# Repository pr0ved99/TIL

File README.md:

# TIL · 이영현의 기술 학습 기록

SSAFY 임베디드 로봇 트랙에서 시작한 학습 기록입니다. 데이터시트에서 읽은 동작을 보드에서 확인하고, 실험을 다시 해 볼 수 있도록 코드와 관측 결과를 함께 남깁니다.

## 대표 프로젝트 · Tracked Mobile Robot

브라우저의 무선 주행 명령이 STM32를 거쳐 좌우 궤도를 움직이는 로봇입니다. 프로젝트 README에서 실제 차체의 움직임, 펌웨어의 정지 판단, Gazebo 속 자율주행을 각각 확인할 수 있습니다. **[프로젝트 열기](https://github.com/pr0ved99/TIL/tree/agent/dual-encoder-bringup/Projects/Tracked_Mobile_Robot#readme)**

| 궁금한 점 | 바로 보기 |
| --- | --- |
| 실제 로봇은 어떻게 움직이나요? | [카펫 주행·비상정지·복구 MP4 (2분 29초)](https://raw.githubusercontent.com/pr0ved99/TIL/refs/heads/agent/dual-encoder-bringup/Projects/Tracked_Mobile_Robot/assets/videos/wifi_mvp/2026-10-24/final/TMR_MVP_Final_2026-10-24.mp4) |
| 정지 명령을 받으면 출력이 언제 꺼지나요? | [STM32 두 PWM의 차단 파형과 측정 기준](https://github.com/pr0ved99/TIL/blob/agent/dual-encoder-bringup/Projects/Tracked_Mobile_Robot/docs/verification/10_STM32_Active_DISARM_Shutdown_Latency_Test_Report_2026-08-04_ko.md) |
| 시뮬레이션에서 로봇은 벽을 어떻게 우회하나요? | [Nav2와 학습 기반 제어의 경로 비교](https://github.com/pr0ved99/TIL/blob/agent/dual-encoder-bringup/Projects/Tracked_Mobile_Robot/docs/verification/48_Simulation_Gate02_2026-11-24_ko.md) |

## 주제별 기록

| 주제 | 찾아볼 내용 |
| --- | --- |
| 임베디드 | [STM32 보드 실습](Embedded/STM32/) · [CAN](Embedded/STM32/CAN/) · [FreeRTOS](Embedded/STM32/RTOS/) · [ESP32-S3](Embedded/ESP32-S3/) · [Jetson](Embedded/Jetson/) |
| 로보틱스 | [ROS 2](Robotics/ROS2/) · [VSLAM](Robotics/VSLAM/) |
| 인공지능 | [강화학습](AI/Reinforcement_Learning/) |
| 개발 기초와 도구 | [Git](CS/Git/) · [운영체제](CS/Operating_System/) · [개발 도구](Tools/) |
| 알고리즘 | [Daily Algorithm](https://github.com/pr0ved99/daily-algorithm)에서 C++ 문제 풀이와 구현 연습을 관리합니다. |

2026년 상반기에 세운 목표는 AI 의존도를 줄이고 데이터시트를 직접 읽어 기술적 판단을 내리는 것입니다. 매일 배운 것을 제 언어로 기록하고, 다른 사람이 동작 원리와 선택 이유를 따라갈 수 있게 쓰려고 합니다. [학습 로드맵](Career-Roadmap/Goal_Roadmap.md)

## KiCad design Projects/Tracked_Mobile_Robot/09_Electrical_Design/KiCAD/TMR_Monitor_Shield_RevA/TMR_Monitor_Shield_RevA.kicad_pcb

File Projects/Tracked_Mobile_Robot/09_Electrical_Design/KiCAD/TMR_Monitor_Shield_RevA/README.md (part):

# TMR Monitor Shield RevA — 노트북 설계 시작점

**11/28 필터 재배치와 아랫면 접지.** R1~R6, C1~C3, TP3~TP6의 위치 또는 방향을 바꾸고 B.Cu에 공통 GND 면을 채웠다. 필터에서 ADC 헤더까지 왼쪽 온도는 51.03 → 21.91 mm, 왼쪽 전류는 43.52 → 34.85 mm, 오른쪽 전류는 44.31 → 25.75 mm다. 오른쪽 온도는 8.66 mm다. 재배선 후 미배선·DRC 위반·회로도 대조 오류는 각 0건이다. [배선 근접 구간 확대 · 품질 검토 2쪽](exports/TMR_Monitor_Shield_RevA_quality_audit.pdf) · [기능별 배치 전후 PDF](exports/TMR_Monitor_Shield_RevA_functional_placement_review.pdf) · [전체 배선 PDF](exports/TMR_Monitor_Shield_RevA_routing_review.pdf) · [검사와 비교 원본](../../../assets/logs/pcb_design/2026-11-28_filter_relayout/README.md)

### 재배치 이전의 검토와 설계 이력

**11/28 기능별 부품 배치 재검토.** 커넥터 위치와 K1 전·후단 분압기, U1·C7, 오른쪽 온도 필터 C4는 유지할 후보로 판단했다. 왼쪽 온도 C3에서 CN7까지 신호는 51.03 mm, GND는 103.27 mm다. 첫 비교안은 R4 출력·C3를 CN7-35 가까이에 배치하고 접지 경로를 단축하는 것이다. 이어서 두 전류 필터의 출력 방향과 J3·J4의 공통 GND를 비교한다. 길이는 저장된 PCB의 배선을 따라 측정했으며 잡음 성능은 제작 후 확인한다. [기능별 배치도와 C3·C4 실제 경로 · 3쪽](../../../assets/logs/pcb_design/2026-11-28_filter_relayout/before/exports/TMR_Monitor_Shield_RevA_functional_placement_review.pdf) · [58개 패드 쌍의 배선 길이와 직선거리](../../../assets/logs/pcb_design/2026-11-28_filter_relayout/before/reports/functional_placement_paths.csv)

**11/28 CAN 트랜시버 배치 결정.** 쉴드에는 STM32용 1개를, ESP32 가까운 만능기판에는 ESP32용 1개를 배치한다. 보유 MCU-230 실측은 약 16 × 14 mm이며, 16 mm 변에 단자 6개가 한 줄로 있다. 기존 NUCLEO는 CN7·CN10 헤더로 만능기판에 고정되어 있다. 쉴드의 J1·J2는 이 두 헤더에 결합하며 H1~H3은 보조 고정용이다. H3 중심 단면에서 M3 체결 공간을 확보하면 J3까지 11.00 mm, H3을 비워 두면 기판 외곽부터 J3까지 18.65 mm다. 빈 홀 위로 모듈 몸체가 지나가는 배치는 후보로 유지한다. 핀 피치·가장자리 여백·높이와 전체 외곽을 대조해 위치를 결정한다. CAN 회로는 설계 전이다. [CAN 연결 계획](../../19_CAN_GPIO_and_Connector_Contract_2026-10-23_ko.md) · [모듈 외형 비교](../../../assets/logs/pcb_design/2026-11-28_can_header_fit/mcu230_body_fit.pdf) · [MCU-230용 1×6 커넥터 한 줄 가배치](../../../assets/logs/pcb_design/2026-11-28_can_header_fit/header_fit.pdf)

**11/28 배선 품질 재검토.** J3·J4 공통 GND 72.00 mm와 C3의 신호/귀환 51.03/103.27 mm를 우선 비교 대상으로 확인했다. 활성 DRC·ERC 및 회로도 대조는 0건이다. 발주 전 실크의 초안 표기, 하네스, 제조 규칙을 대조한다. [세 검토표 대조 결과 · 7쪽](../../../assets/logs/pcb_design/2026-11-28_filter_relayout/before/exports/TMR_Monitor_Shield_RevA_quality_audit.pdf)

**11/28 쉴드 전체 배선 완료.** 활성 22개 네트의 94개 패드가 회로도대로 연결됐다. 미배선 0건, DRC 위반 0건, 회로도 대조 오류 0건이다. 제작 전 검토에서 커넥터 1번 방향과 1:1 실물 장착, 제조 규칙과 Gerber·드릴을 확인한다. [전체 배선 검토 PDF · 양면 배선, 온도 채널, 전원·GND, 검사 결과](../../../assets/logs/pcb_design/2026-11-28_filter_relayout/before/exports/TMR_Monitor_Shield_RevA_routing_review.pdf)

**11/28 오른쪽 전류 ADC와 시험점.** R2.2에서 아랫면으로 C2.1까지 연결했다. C2.1에서 윗면으로 가는 갈래는 시험점 TP4.1에, 아랫면에서 비아 하나를 거쳐 윗면으로 오는 갈래는 CN7-36(PC1)에 닿는다. 네 패드의 연결에 이어 J4.2·C2.2도 기존 GND에 연결했다. [전류 배선 확대도 6~7쪽](../../../assets/logs/pcb_design/2026-11-28_filter_relayout/before/exports/TMR_Monitor_Shield_RevA_current_routing.pdf)

**11/28 오른쪽 전류 센서 출력.** J4.3에서 필터 저항 R2.1까지 폭 0.25 mm로 연결했다. 기존 아랫면 GND 위를 지나 비아에서 층을 바꾸고, 윗면 분압 신호 아래를 통과한다. [오른쪽 센서 출력과 교차점 · 전류 확대도 5쪽](../../../assets/logs/pcb_design/2026-11-28_filter_relayout/before/exports/TMR_Monitor_Shield_RevA_current_routing.pdf)

**11/28 왼쪽 전류 센서 J3.** J3.3의 VIOUT는 왼쪽 모터 전류에 따라 변하는 센서 출력 전압이다. J3.3과 필터 저항 R1.1 사이를 선폭 0.25 mm, 길이 42.66 mm의 윗면 배선으로 연결했다. 가장 가까운 다른 네트는 J3.2(GND)로 구리 가장자리 사이가 0.704 mm다. R1 뒤에서는 R1.2·C1.1·TP3.1·CN7-38(PC0)이 하나의 ADC 신호로 이어진다. PC0으로 가는 배선은 관통 비아 하나를 사용한다.

J3.2와 C1.2는 아랫면 구리로 C6.2를 거쳐 CN7-20 GND에 연결했다. CN7-16에서 J3.1로 가는 3.3 V 전원선은 아랫면을 지난 뒤 비아 하나를 거쳐 윗면에서 센서에 닿는다. J3의 세 핀 모두 PCB에서 연결을 확인했다. [센서 출력 1쪽 · ADC 배선 2쪽 · GND 귀환 3쪽 · 3.3 V 전원 4쪽](../../../assets/logs/pcb_design/2026-11-28_filter_relayout/before/exports/TMR_Monitor_Shield_RevA_current_routing.pdf) · [검사 결과](../../../assets/logs/pcb_design/2026-11-28_filter_relayout/before/reports/design_review.json)

**11/28 전단·후단 ADC 출력 배선.** U2.3에서 R11.1과 NUCLEO CN7-32까지 전단 전압 신호를 윗면으로 연결했다. R11은 ADC와 같은 노드에 붙는 47 kΩ 풀다운 저항이다. 후단도 U2.6·R16.1·CN7-34를 윗면에 연결했다. 후단 신호 총길이는 37.55 mm, 다른 네트 구리와의 최소 간격은 0.325 mm다. R11.2와 R16.2는 공용 비아를 통해 CN7-20의 기존 GND에 연결했다. U1.1에서 U2.4(SEL2)와 U2.1(SEL1)로 가는 제어선도 연결했다. 두 감지 경로는 함께 켜지고 꺼지며 각기 다른 ADC 입력으로 이어진다. 제어선 배선 직후의 보드 전체 미배선은 32건이었다. [전단 3쪽 · 후단 4쪽 · 풀다운 5쪽 · 제어선 6쪽](../../../assets/logs/pcb_design/2026-11-28_filter_relayout/before/exports/TMR_Monitor_Shield_RevA_voltage_routing.pdf) · [검사 결과](../../../assets/logs/pcb_design/2026-11-28_filter_relayout/before/reports/design_review.json)

**11/27 전압 감지 입력 배선.** K1 전단은 J7.2 → R7 → R8 → 분압점 → R10 → U2.2, 후단은 J8.2 → R12 → R13 → 분압점 → R15 → U2.5로 이어진다. C5·C6은 각 분압점과 GND 사이의 필터다. 커넥터에서 각 분압기로 가는 윗면 신호선의 폭은 0.25 mm다. 아랫면에서는 J7.1을 C5.2에, J8.1을 C6.2에 폭 0.30 mm로 배선해 두 커넥터의 GND가 CN7-20까지 이어진다. 이 단계에서 DRC 위반과 회로도 대조 오류는 0건이었고, 전체 미배선은 40건이었다. [전압 감지 배선 확대도](../../../assets/logs/pcb_design/2026-11-28_filter_relayout/before/exports/TMR_Monitor_Shield_RevA_voltage_routing.pdf) · [검사 결과](../../../assets/logs/pcb_design/2026-11-28_filter_relayout/before/reports/design_review.json) · [후단 배선과 C2 패드 간격](../../../assets/logs/pcb_design/2026-11-27_voltage_routing_review/voltage_clearance_detail.pdf)

**11/27 전체 부품 배치.** 정식 PCB에 회로 부품 40개와 기구 전용 H1~H3(Ø3.2 mm 비도금 홀)를 배치했다. C4는 CN7-37 옆으로 옮겼고 K1 전단 R7~R11·후단 R12~R16의 20개 패드가 회로도와 일치한다. 배치 완료 시점의 미배선은 72건이었다. [윗면 배치도](../../../assets/logs/pcb_design/2026-11-28_filter_relayout/before/exports/TMR_Monitor_Shield_RevA_placement.pdf) · [거리와 검사 결과](../../../assets/logs/pcb_design/2026-11-28_filter_relayout/before/reports/design_review.json)

**11/27 전압 감시기·스위치 배치 이력.** U1·C7(220 nF)과 U2·C8(100 nF)을 왼쪽 CN7 근처 윗면에 배치했다. J1-32·J1-34·J2-7 패드의 네트를 회로도와 맞췄다. 이때 R7~R16의 위치는 미정이었다. [정식 배치도](../../../assets/logs/pcb_design/2026-11-28_filter_relayout/before/exports/TMR_Monitor_Shield_RevA_placement.pdf) · [패드 연결과 좌표](../../../assets/logs/pcb_design/2026-11-28_filter_relayout/before/reports/design_review.json)

**11/27 필터 커패시터.** C1~C6은 보유 중인 Vishay `K104K15X7RF53H5`(100 nF)를 쓴다. 회로도와 PCB에 제조사·품번·자료 링크를 넣고 리드 피치 5.00 mm, 홀 Ø0.80 mm인 공통 풋프린트를 지정했다. C5는 전단 분압점, C6은 후단 분압점의 필터로 PCB에 가배치했다. 다음 저항 배치에서 분압점에서 필터까지의 경로를 확인한다. [부품별 BOM](bom_candidates.csv) · [윗면 배치도](../../../assets/logs/pcb_design/2026-11-28_filter_relayout/before/exports/TMR_Monitor_Shield_RevA_placement.pdf)

**11/27 전압 커넥터.** 쉴드 회로도의 J7·J8에 JST PA `B02B-PASK-1` 풋프린트를 지정했다. 사용자가 지정한 USB 반대쪽 가장자리에 J7·J8을 가배치했다. 윗면 몸체 사이가 9.0 mm이고 두 하네스는 위로 뽑아 같은 가장자리로 넘긴다. 두 자리 모두 상부 개방이며 24 AWG 전선을 USB 반대쪽으로 넘길 때 간섭이 없었다. PA 입고 후 걸쇠 접근과 두 하네스 탈착을 확인한다. [윗면 배치도](../../../assets/logs/pcb_design/2026-11-28_filter_relayout/before/exports/TMR_Monitor_Shield_RevA_placement.pdf) [회로도 PDF](exports/TMR_Monitor_Shield_RevA_schematic.pdf) · [풋프린트와 도면](BOM_Bench_Check_2026-11-27_ko.md) · [검사 결과](../../../assets/logs/pcb_design/2026-11-28_filter_relayout/before/reports/design_review.json)

**11/12 출력 이력:** [기본 경로의 최신 회로도 PDF](exports/TMR_Monitor_Shield_RevA_schematic.pdf)를 현재 저장 회로도에서 다시 생성했다. 40부품과 PWR_FLAG 2개, J7/J8을 포함한 6개 측정 포트가 반영되어 있다. 왼쪽 아래 `04 VOLTAGE INPUTS – TWO CHANNELS` 영역의 위쪽은 J7/VBAT_SENSE, 아래쪽은 J8/VMOTOR_SENSE다. 11/7 게시본과 본문·렌더링이 일치하며 CAD 원본은 변경하지 않았다. [확인 기록](../../../assets/logs/pcb_design/2026-11-12_export_sync/README.md).

**11/20 확인:** 위 회로도 PDF와 [보고서](reports/README.md)를 기본 열람 경로로 사용한다. 회로도는 J7/J8을 포함한 40부품, PCB는 22풋프린트의 초기 배치다. 제작 및 실측은 준비 전이다. [현재 실행 순서](../../../docs/handoff/CURRENT_SESSION_CONTEXT.md). 아래 날짜별 연결·배치 설명은 당시 상태다.

**작성 이력 · 2026-11-07:**

전압2채널·공통 제어와PWR_FLAG2개까지 사용자 작성 완료,40부품·활성22net·기존 설정 ERC0/0이다. Codex가 마감 시 오래된 주석/제목란만 갱신했다. [최신 PDF·검증](../../../assets/logs/pcb_design/2026-11-07_cad_closeout/README.md). 다음은 수집·필터 표와 포트·전원 조건표이며 풋프린트/기구·PCB는 그 뒤다. 후보 BOM은40부품으로 갱신했으나 구매/제작 승인은 아니다. 아래는 당시 이력이다.

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
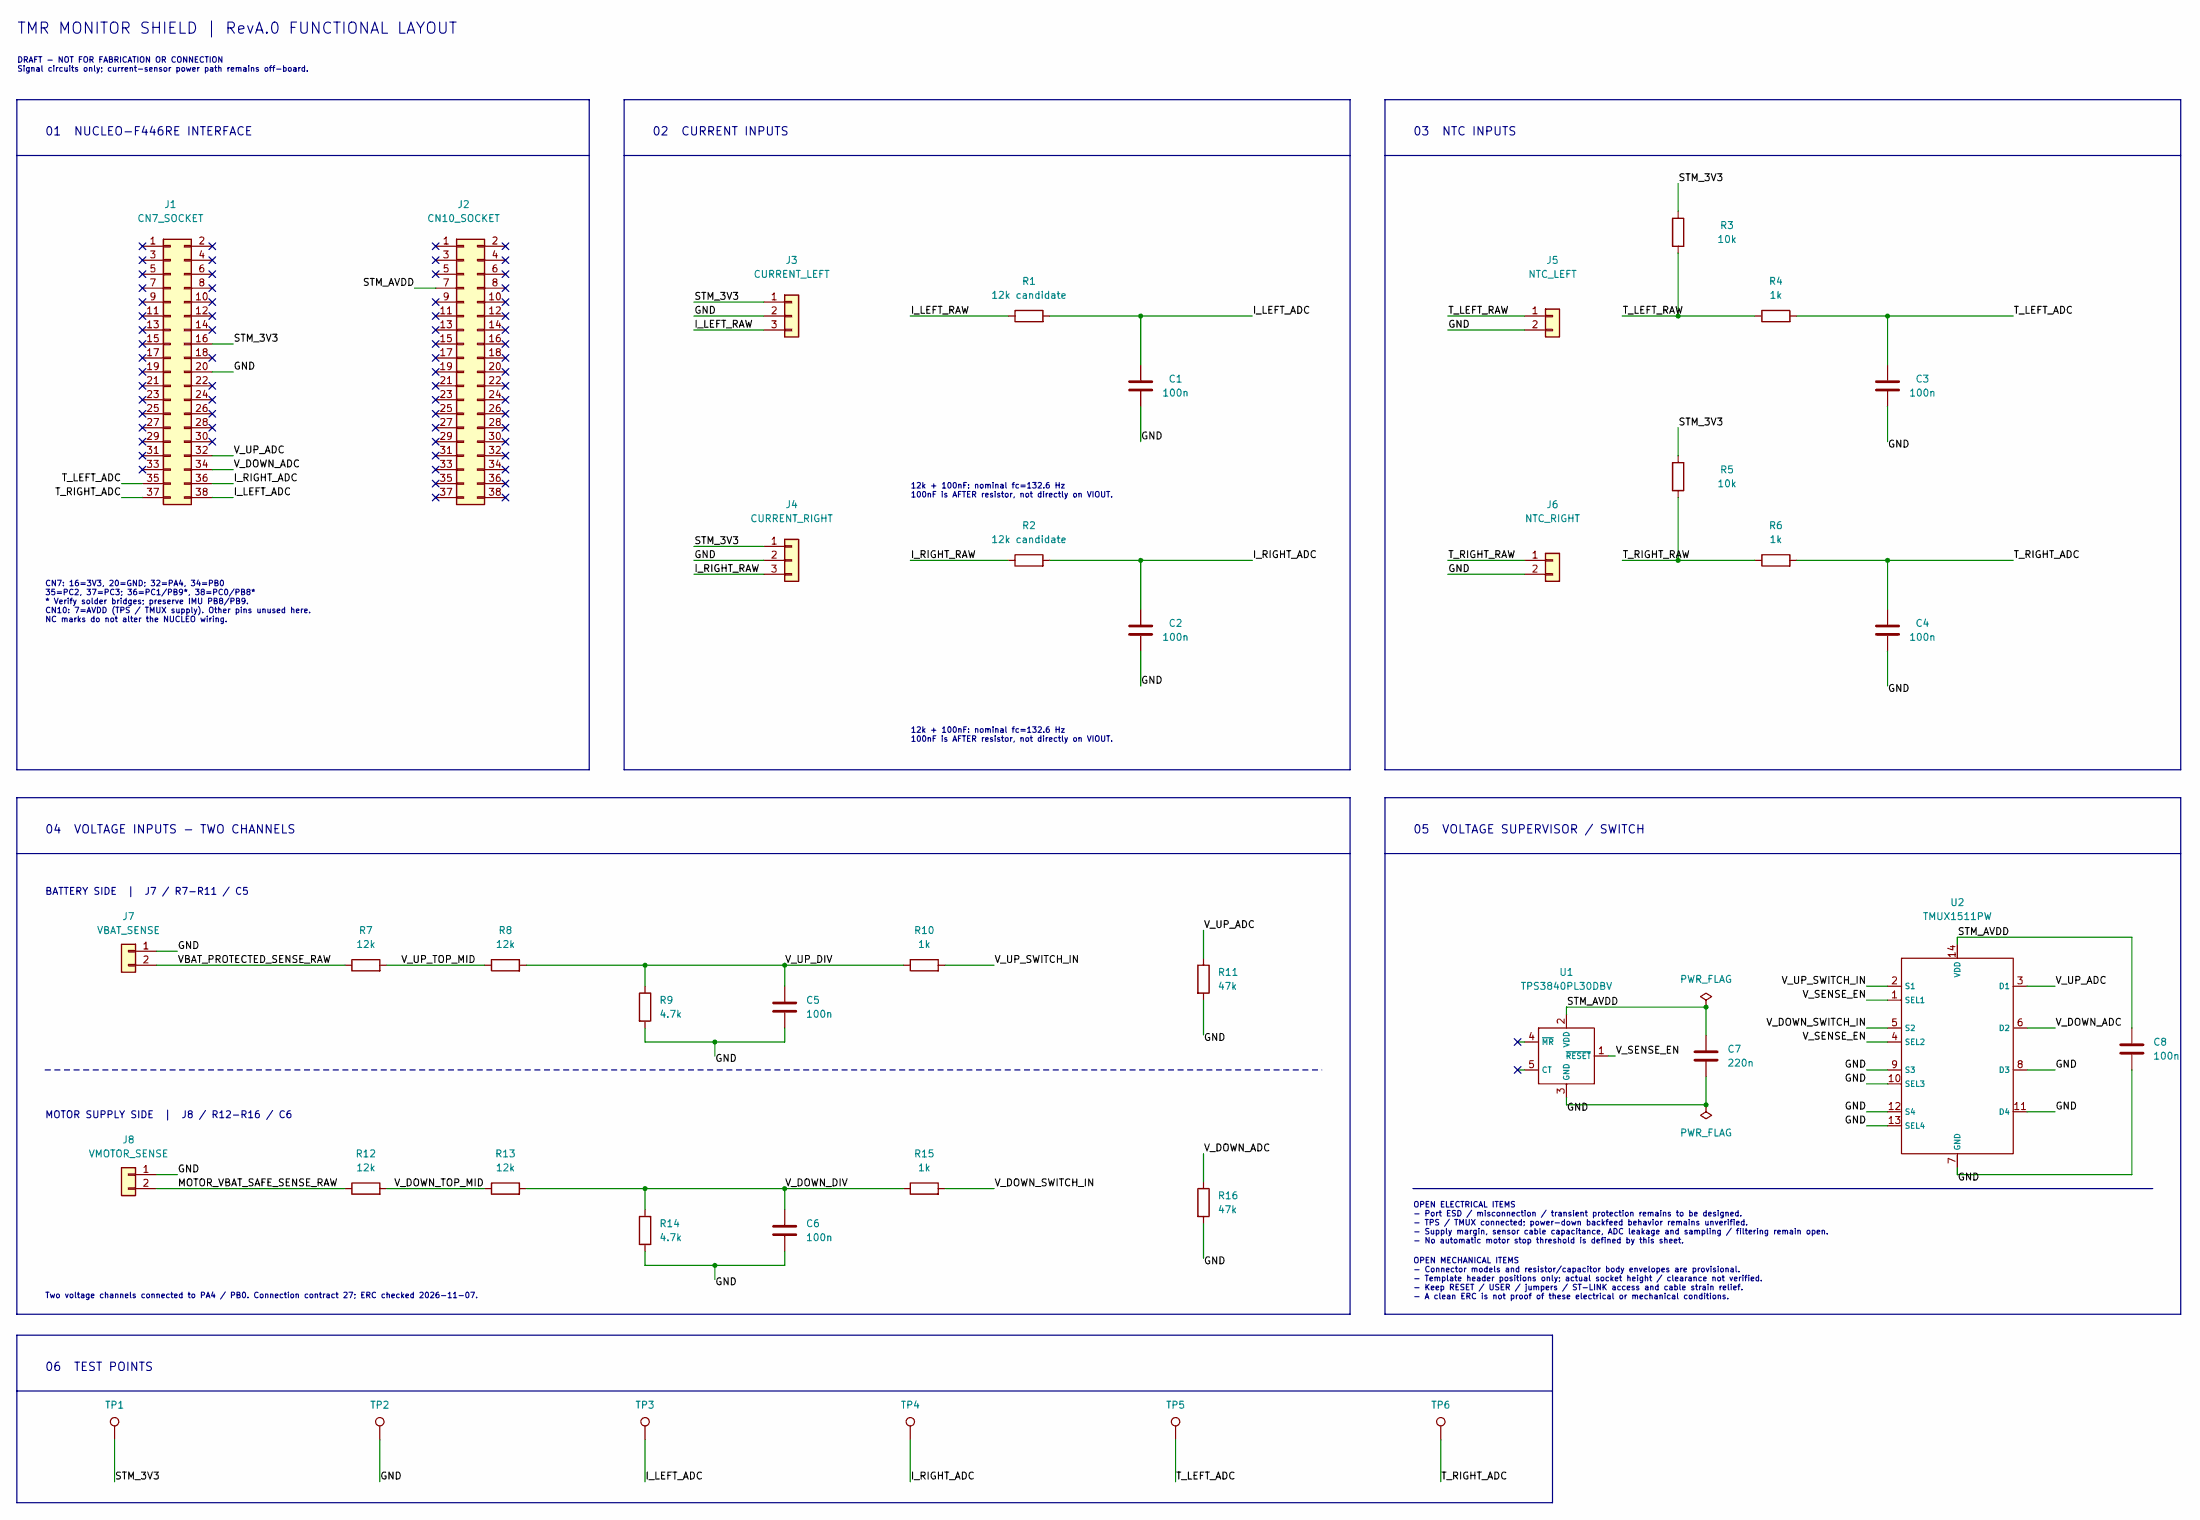
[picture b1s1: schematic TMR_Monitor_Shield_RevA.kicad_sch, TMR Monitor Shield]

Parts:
C1, C2, C3, C4, C5, C6: 100n; C_Disc_D5.1mm_W3.2mm_P5.00mm; MPN K104K15X7RF53H5
C7: 220n; C_0805_2012Metric; MPN C0805C224K5RACTU
C8: 100n; C_0805_2012Metric; MPN C0805C104K5RACTU
J1: CN7_SOCKET; PinSocket_2x19_P2.54mm_Vertical
J2: CN10_SOCKET; PinSocket_2x19_P2.54mm_Vertical
J3: CURRENT_LEFT; JST_XH_B3B-XH-A_1x03_P2.50mm_Vertical
J4: CURRENT_RIGHT; JST_XH_B3B-XH-A_1x03_P2.50mm_Vertical
J5: NTC_LEFT; JST_XH_B2B-XH-A_1x02_P2.50mm_Vertical
J6: NTC_RIGHT; JST_XH_B2B-XH-A_1x02_P2.50mm_Vertical
J7: VBAT_SENSE; JST_PA_B02B-PASK-1_1x02_P2.00mm_Vertical
J8: VMOTOR_SENSE; JST_PA_B02B-PASK-1_1x02_P2.00mm_Vertical
R1, R2: 12k candidate; R_Axial_DIN0207_L6.3mm_D2.5mm_P7.62mm_Horizontal
R3, R5: 10k; R_Axial_DIN0207_L6.3mm_D2.5mm_P7.62mm_Horizontal
R4, R6: 1k; R_Axial_DIN0207_L6.3mm_D2.5mm_P7.62mm_Horizontal
R7, R8, R12, R13: 12k; R_0805_2012Metric; MPN TNPW080512K0BEEA
R9, R14: 4.7k; R_1206_3216Metric; MPN TNPW12064K70BEEA
R10, R15: 1k; R_2512_6332Metric; MPN RNCF2512BKE1K00
R11, R16: 47k; R_0805_2012Metric; MPN TNPW080547K0BEEA
TP1: STM_3V3; TestPoint_THTPad_D1.5mm_Drill0.7mm
TP2: GND; TestPoint_THTPad_D1.5mm_Drill0.7mm
TP3: I_LEFT_ADC; TestPoint_THTPad_D1.5mm_Drill0.7mm
TP4: I_RIGHT_ADC; TestPoint_THTPad_D1.5mm_Drill0.7mm
TP5: T_LEFT_ADC; TestPoint_THTPad_D1.5mm_Drill0.7mm
TP6: T_RIGHT_ADC; TestPoint_THTPad_D1.5mm_Drill0.7mm
U1: TPS3840PL30DBV; SOT-23-5
U2: TMUX1511PW; TSSOP-14_4.4x5mm_P0.65mm

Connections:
/GND: C1.2, C2.2, C3.2, C4.2, C5.2, C6.2, C7.2, C8.2, J1.20, J3.2, J4.2, J5.2, J6.2, J7.1, J8.1, R9.2, R11.2, R14.2, R16.2, TP2.1, U1.3 (GND), U2.7 (GND), U2.8 (D3), U2.9 (S3), U2.10 (SEL3), U2.11 (D4), U2.12 (S4), U2.13 (SEL4)
/I_LEFT_ADC: C1.1, J1.38, R1.2, TP3.1
/I_LEFT_RAW: J3.3, R1.1
/I_RIGHT_ADC: C2.1, J1.36, R2.2, TP4.1
/I_RIGHT_RAW: J4.3, R2.1
/MOTOR_VBAT_SAFE_SENSE_RAW: J8.2, R12.1
/STM_3V3: J1.16, J3.1, J4.1, R3.1, R5.1, TP1.1
/STM_AVDD: C7.1, C8.1, J2.7, U1.2 (VDD), U2.14 (VDD)
/T_LEFT_ADC: C3.1, J1.35, R4.2, TP5.1
/T_LEFT_RAW: J5.1, R3.2, R4.1
/T_RIGHT_ADC: C4.1, J1.37, R6.2, TP6.1
/T_RIGHT_RAW: J6.1, R5.2, R6.1
/VBAT_PROTECTED_SENSE_RAW: J7.2, R7.1
/V_DOWN_ADC: J1.34, R16.1, U2.6 (D2)
/V_DOWN_DIV: C6.1, R13.2, R14.1, R15.1
/V_DOWN_SWITCH_IN: R15.2, U2.5 (S2)
/V_DOWN_TOP_MID: R12.2, R13.1
/V_SENSE_EN: U1.1 (~RESET), U2.1 (SEL1), U2.4 (SEL2)
/V_UP_ADC: J1.32, R11.1, U2.3 (D1)
/V_UP_DIV: C5.1, R8.2, R9.1, R10.1
/V_UP_SWITCH_IN: R10.2, U2.2 (S1)
/V_UP_TOP_MID: R7.2, R8.1

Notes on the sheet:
MOTOR SUPPLY SIDE | J8 / R12-R16 / C6
02 CURRENT INPUTS
CN7: 16=3V3, 20=GND; 32=PA4, 34=PB0 35=PC2, 37=PC3; 36=PC1/PB9*, 38=PC0/PB8* * Verify solder bridges; preserve IMU PB8/PB9. CN10: 7=AVDD (TPS / TMUX supply). Other pins unused here. NC marks do not alter the NUCLEO wiring.
06 TEST POINTS
BATTERY SIDE | J7 / R7-R11 / C5
12k + 100nF: nominal fc=132.6 Hz 100nF is AFTER resistor, not directly on VIOUT.
03 NTC INPUTS
OPEN MECHANICAL ITEMS - Connector models and resistor/capacitor body envelopes are provisional. - Template header positions only; actual socket height / clearance not verified. - Keep RESET / USER / jumpers / ST-LINK access and cable strain relief. - A clean ERC is not proof of these electrical or 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
04 VOLTAGE INPUTS - TWO CHANNELS
Two voltage channels connected to PA4 / PB0. Connection contract 27; ERC checked 2026-11-07.
01 NUCLEO-F446RE INTERFACE
DRAFT - NOT FOR FABRICATION OR CONNECTION Signal circuits only; current-sensor power path remains off-board.
05 VOLTAGE SUPERVISOR / SWITCH
TMR MONITOR SHIELD | RevA.0 FUNCTIONAL LAYOUT
OPEN ELECTRICAL ITEMS - Port ESD / misconnection / transient protection remains to be designed. - TPS / TMUX connected; power-down backfeed behavior remains unverified. - Supply margin, sensor cable capacitance, ADC leakage and sampling / filtering remain open. - No automatic motor stop threshold i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

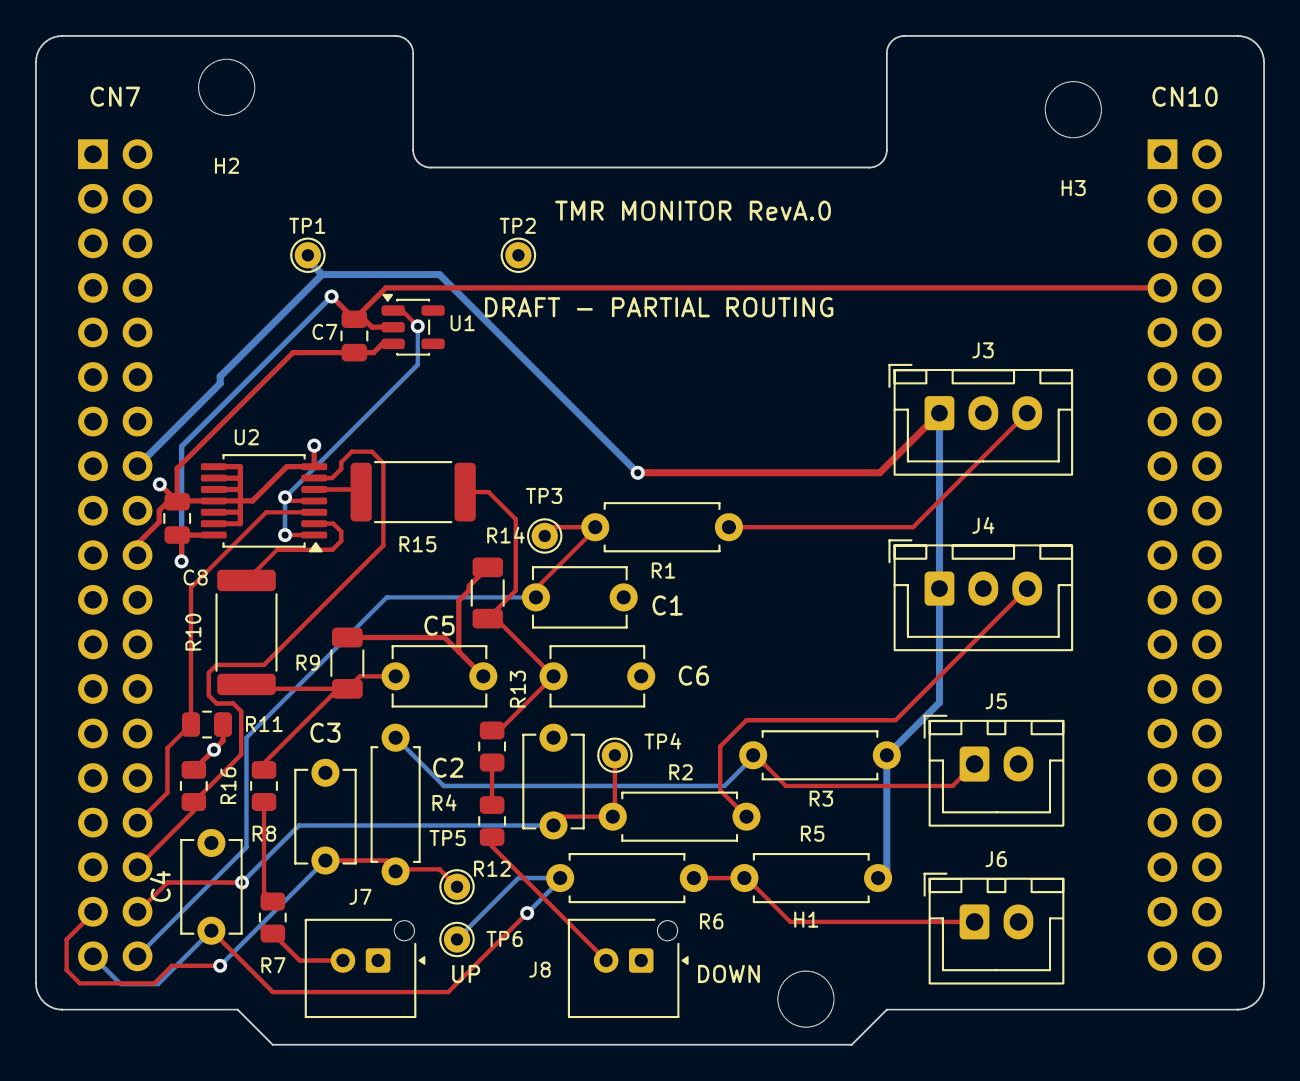
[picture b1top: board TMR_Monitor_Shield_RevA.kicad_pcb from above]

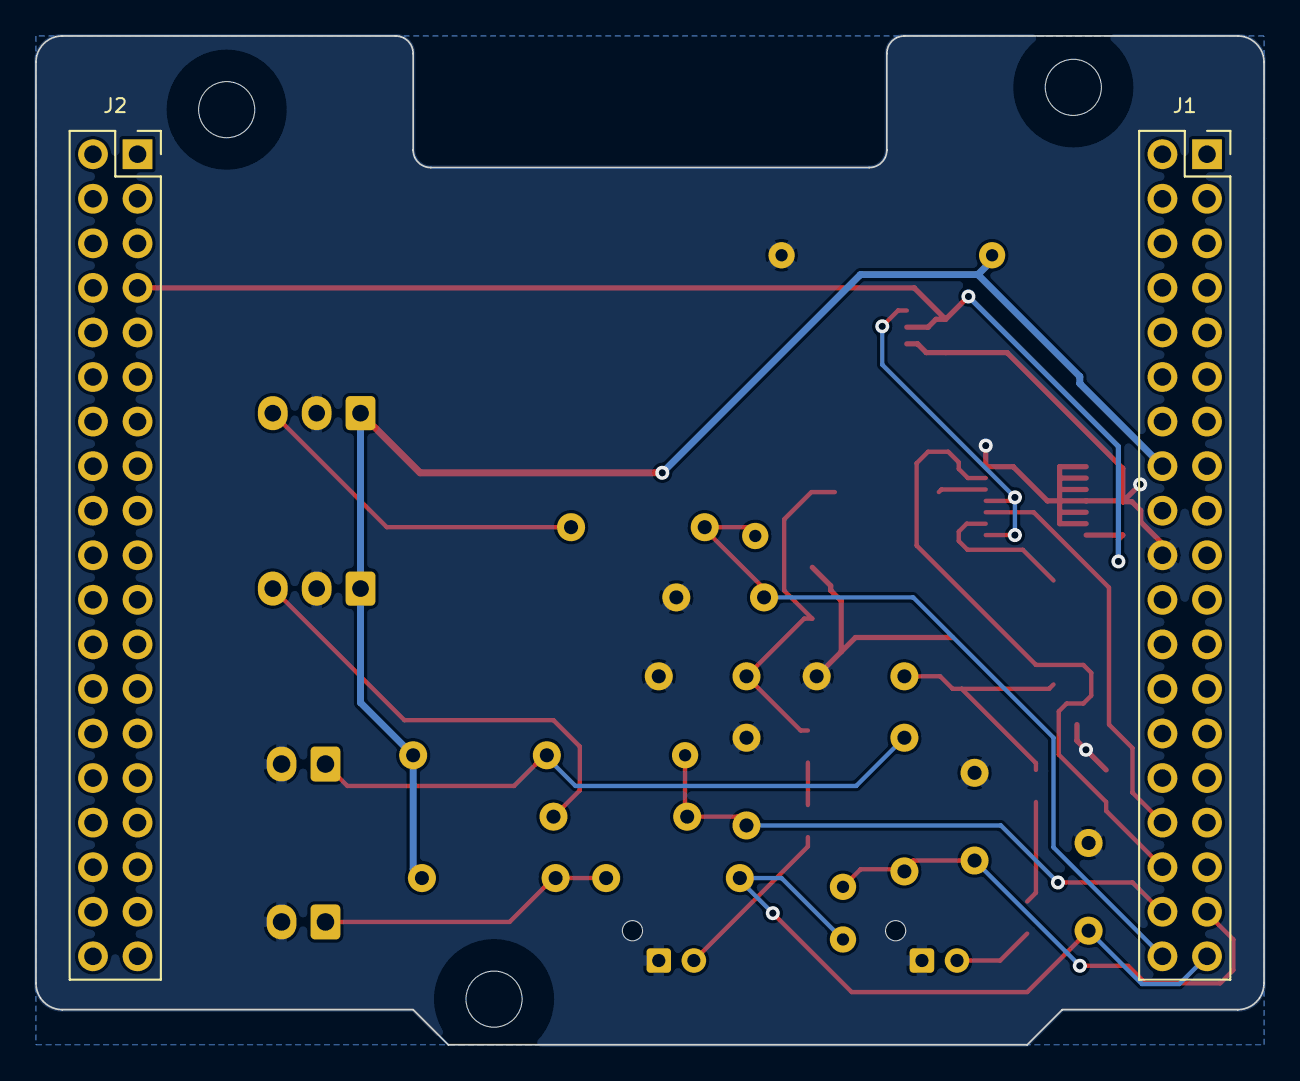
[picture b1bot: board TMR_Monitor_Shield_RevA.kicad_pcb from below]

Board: 2 copper layers, 70.0 x 57.5 mm, 43 parts (2 on the bottom side), 22 nets.

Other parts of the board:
H1, H2, H3: MountingHole; MountingHole_3.2mm_M3

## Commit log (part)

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2026-01-03 docs: 리드미 작성 및 깃 협업 가이드 추가
2026-01-03 Fix link to Daily Algorithm Repository
2026-01-03 Git 기초 지식을 공부 / v1
2026-01-03 docs: Git 기초 가이드 어투 수정 및 TIL 스타일로 리팩토링
2026-01-03 style: fix typos
2026-01-03 docs: 커밋 컨벤션(Conventional Commits) 가이드 추가
2026-01-03 fix: 중첩되는 내용의 파일 정리
2026-01-03 docs: 협업에 필요한 공부 업로드
2026-01-03 fix: reconstruction
2026-01-03 fix: 자잘한 오타 수정...
    브렌치도 만들어서 수정했지만 main과 merge하면 보이는 오타들...
    진짜 merge...
2026-01-03 Revise README structure and add new content
    Updated README to include new sections and images.
2026-01-04 docs: 프로젝트 제안서 초안과 기타 마크다운 파일 생성
2026-01-05 fix: 명세서에 부합하는 제안서로 수정 1
2026-01-06 Refine team roles and responsibilities in proposal
2026-01-17 프로젝트 이름 최종 수정
2026-01-17 docs: 로봇 조립도, 폭파도 및 층별 도면 프리뷰 이미지 추가
2026-01-17 docs: 하드웨어 설계 개요 및 조립/폭파도 이미지 추가
2026-01-17 docs: 6구 퓨즈박스 중심 전원 분배 계통 정의
2026-01-17 docs: 구매 목록 시트 기반 하드웨어 BOM 최신화
2026-01-17 docs: 부품 명세(BOM) 최신화 및 상세 핀 맵(PinMapping) 추가
2026-02-22 Delete Project/PET_Ner directory
    올바른 Direction으로 이전 예정
2026-02-22 docs: Add Ubuntu STM32CubeIDE 2.0 & CubeMX installation guide
2026-02-22 docs: Update README, .gitignore and Gitignore_Setup.md for STM32 environment
2026-02-22 refactor: Reorganize STM32 docs into Theory and Practice & rename Blinky tutorial
2026-02-22 docs: Add HAL vs LL comparison & new tutorial with assets directory
2026-02-22 docs: Rename theory docs with numeric prefixes & add F446RE hardware overview
2026-02-22 docs: Fix image extension for usb cable from png to jpeg
2026-02-22 docs: Format hardware overview with tables for better readability
2026-02-22 docs: Add LL Hybrid Blinky tutorial in Practice folder
2026-02-22 docs: Add EXTI push button interrupt tutorial in Practice folder
2026-02-22 docs: Rewrite PWM tutorial in TIL (declarative) style
2026-02-22 feat: Add F446RE EXTI and PWM project files
2026-02-22 chore: Set up Reinforcement Learning directory structure
2026-02-22 chore: Set up Jira directory structure
2026-02-22 feat: Add STM32 F446RE PWM tutorial markdown file.
2026-02-22 feat: Initialize Python virtual environment and install project dependencies.
2026-02-22 docs: Translate README.md to Korean
2026-04-08 add vslam study directory structure
2026-04-08 add d435i vslam implementation plan
2026-04-08 add jetson orin nano docker study docs
2026-04-09 docs: add outdoor trash robot development roadmaps
2026-04-11 docs: reorganize vslam docs and daily logs
2026-04-11 feat: add d435i debugging and mapping scripts
2026-04-11 docs: add d435i evidence assets
2026-04-11 fix: relax rtabmap rgbd odometry startup settings
2026-04-11 docs: explain viewer and rtabmap realtime gap
2026-04-11 docs: add odom comparison and update rtabmap status
2026-04-11 docs: add imu axis notes and refresh progress
2026-04-13 docs: add pre-arrival fusion plan and model exports
2026-04-13 Update VSLAM RTAB-Map workflow and sprint docs
2026-04-14 Add RTAB-Map retest logs and BNO08x placement guide
2026-04-17 Add Jetson VSLAM bring-up docs
2026-04-21 Add Jetson RTAB-Map benchmark assets and templates
2026-04-21 Add BNO08x Jetson bring-up and viewer tools
2026-04-21 Add Jetson Docker RTAB-Map stack and diagnostics
2026-04-21 Update Jetson VSLAM indexes and progress docs
2026-04-23 Add Jetson BNO08x IMU comparison benchmark
2026-04-23 Add trashbot URDF RViz model draft
2026-04-23 Add VSLAM daily index
2026-04-23 Add D435i RTAB-Map VSLAM manual
2026-04-23 Add 2026-04-23 VSLAM CAD preparation log
2026-04-23 Add Jetson Docker VSLAM docs tools and small turtle prep
2026-04-24 feat(vslam): add small turtle urdf sensor prep
2026-04-25 docs: record small turtle urdf planning
2026-04-27 docs: update mari gazebo model progress
2026-04-27 feat: add Mari RViz TF checks and Jetson handoff
2026-04-28 feat(vslam): add Mari Gazebo RTAB-Map baseline
2026-05-01 feat: add Mari Gazebo localization validation
    Add Mari Gazebo sensor, encoder, EKF, RTAB-Map, park-world validation assets and documentation.
2026-05-04 Add Mari Nav2 saved-map navigation workflow
2026-05-05 docs: record Jetson GPS UART troubleshooting
2026-05-07 docs(vslam): record rtabmap multisession db reuse
    Refs S14P31C205-678
    Refs S14P31C205-679
2026-05-11 docs(vslam): record S14P31C205-735 Duri validation
2026-05-13 docs(vslam): record S14P31C205-735-1327 Jira backlog updates
2026-05-13 docs(vslam): record S14P31C205-1282 trash pose projection
2026-05-21 docs(vslam): record Duri autonomy progress
2026-05-21 docs(stm32): add CAN FreeRTOS roadmap notes
2026-05-21 docs(os): add dinosaur book learning notes
2026-05-22 docs(esp32): add ESP32-S3 setup notes
2026-05-22 docs(esp32): record RGB LED practice
2026-05-24 docs(cleanup): record laptop git preservation plan
2026-05-24 docs(cleanup): add laptop migration plan
2026-05-24 docs(cleanup): add google drive upload manifest
2026-06-03 docs(robot): add tracked mobile robot design notes
2026-06-04 docs(robot): add handoff for tracked mobile robot
2026-06-07 docs(ros2): add project learning roadmap
2026-06-07 docs(stm32): add can and rtos learning maps
2026-06-07 docs(robot): update tracked robot architecture
2026-06-08 docs(robot): add MDD10A hardware execution plan
2026-06-13 docs: move CS study notes into TIL
2026-06-21 feat: add tracked robot UART MVP tooling
2026-06-22 docs: refresh tracked robot handoff
2026-06-22 Add STM32 UART MVP firmware and validation evidence
2026-06-27 Implement STM32 UART MVP protocol

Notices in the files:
Projects/Tracked_Mobile_Robot/09_Electrical_Design/KiCAD/TMR_Monitor_Shield_RevA/README.md:
- [템플릿 출처·변경 범위](reports/template_provenance.json): KiCad 배포 템플릿, TiZed (2021), CC0. 설치 템플릿에서 파생된 외곽과 헤더 배치를 사용했다.
